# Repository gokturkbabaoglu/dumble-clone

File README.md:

# 12 V gitar amfisi — BF245B JFET + LM386 + TDA2003, ISF ton kontrolü

12 V ile çalışan, 4 Ω 6,5" full range hoparlör süren küçük bir pratik amfisi. Drive, Gain, ISF (US ↔ UK karakter), Volume kontrolleri, Dark/Normal/Bright anahtarı ve kesicili 3,5 mm kulaklık çıkışı var. Tek yüzlü, ev yapımı baskı devre; pot, jak ve LED kartın ön kenarına lehimli.

> Bu repo yalnızca bu 12 V JFET/op-amp amfisi içindir. Lambalı 5F1 amfi projesi ayrıdır.

## Durum (20 Kasım 2026)

- **Güncel kart: kart v5** — [`guncel/kicad/`](guncel/kicad/) (KiCad 10, proje `amfi_yeni.kicad_pro`). KiCad'de sıfırdan yeni tasarım: tellerle çizilmiş şema (ERC 0 hata / 0 uyarı), büyük padli ayak izi kütüphanesi (lazerle boya yakma + asit için), 185 × 96 mm tek yüz (yalnız alt bakır), ince yollar (0,4 mm, aralık 0,4 mm).
- **Açık işler:** 2 bağlantı henüz çizilmedi (U2.4–TOUT, R22–R31). Yollar KiCad'de elle kalınlaştırılıp düzenlenecek.
- Parçalar alındı. Kart henüz basılmadı, devre henüz denenmedi.
- Devre (netlist) Rev 5 + RV4 DRIVE; simülasyonları [`guncel/sim/`](guncel/sim/README.md).

## Klasörler

| Klasör | İçerik |
|---|---|
| [`guncel/kicad/`](guncel/kicad/) | **Güncel KiCad projesi (kart v5):** şema, kart, ayak izi kütüphanesi `amfi_yeni.pretty`, üretim/denetim betikleri |
| [`guncel/sim/`](guncel/sim/README.md) | Micro-Cap 12 simülasyonları: DC, AC, transient, THD, gürültü, empedans/kararlılık, C9/RV4, diğer amfilerle karşılaştırma |
| [`guncel/parca-gorselleri/`](guncel/parca-gorselleri/) | Jak, anahtar ve soğutucu ürün görselleri/ölçü çizimleri |
| [`eski/`](eski/README.md) | Önceki kartlar (v1, v2, v3 taslağı, v4 KiCad/Freerouting) ve araçları — kullanılmıyor, arşiv |

## Kontroller

| Kontrol | Parça | Ne yapar |
|---|---|---|
| Drive | RV4 B2.2K lineer + C9 22µ | JFET katının kazancı: ilk %70 temiz–sıcak, son %30 crunch–overdrive |
| Gain | B100K + R7 15k | LM386 katına giren sinyal; düşükte temiz, yüksekte crunch |
| SW1 | Mavi ON-OFF-ON | Yukarı Bright (470p) / orta Normal / aşağı Dark (3,3n) |
| ISF | B250K | Bir uç US (Fender tipi), öbür uç UK (Marshall tipi) |
| Volume | B500K | Güç katına giden seviye |
| Kulaklık | PJ-324M (kesicili) | Fiş takılınca hoparlör susar; L-pad (10 Ω / 330 Ω) |
| Güç | Kırmızı ON-ON, 6 bacak | Yukarı = açık |

- **Sinyal yolu:** gitar → Q1 BF245B → Gain + Dark/Bright → LM386 (≈38×) → ISF (iki sabit ton yığını arasında geçiş) → Volume → 47k/10k bölücü + ≈6 kHz alçak geçiren → TDA2003 (≈40 dB) → hoparlör / kulaklık
- **Besleme:** 12 V / 2 A adaptör → panel DC jak → TB1 → 1 A sigorta → güç anahtarı → 1N5822 → V12; RC filtrelerle LM386 (100 Ω) ve JFET (1k) beslemeleri ayrılır

## Kablolama

Kabloyla bağlanan parçalar: SW1 (Dark/Normal/Bright), güç anahtarı, panel DC jak ve hoparlör.

- **SW1** → P1 (B), P2 (orta), P3 (A). Bacaklar dikey takılır: üst = A (Dark), orta = ortak, alt = B (Bright). Kol yukarı = Bright.
- **Güç anahtarı** → P4 / P5: tek sütunun orta ve alt bacakları kullanılır (orta = sigortadan sonra, alt = 1N5822'ye). Kol yukarı = açık.
- **DC jak** → TB1, **hoparlör** → TB2 (kulaklık jakının kesici kontağından gelir). Hoparlör kabloları hoparlörde lehimlenir, kablolar burgulanır.

## Parça listesi (takılacak haliyle)

★ = tasarımdan farklı; çalışmayı bozmadığı için böyle bırakıldı (notlar aşağıda).

**Dirençler**

| Değer | Adet | Referanslar |
|---|---|---|
| 1 Ω | 1 | R27 |
| 2,2 Ω | 1 | R26 |
| 10 Ω | 2 | R9, R28 |
| 100 Ω | 1 | R1 |
| 220 Ω | 1 | R25 |
| 330 Ω | 1 | R29 |
| 1k | 1 | R2 |
| 1,2k | 1 | R8 |
| 2,2k | 2 | R3, R31 |
| 4,7k | 1 | R17 |
| 6,8k | 2 | R4, R16 |
| 10k | 4 | R12, R24, R30, R5b ★ |
| 15k | 1 | R7 |
| 22k | 2 | R22, R5a ★ |
| 33k | 1 | R18 |
| 47k | 1 | R23 |
| 91k | 1 | R19 |
| 100k | 3 | R10, R11, R13 |
| 120k | 2 | R15, R20 |
| 150k | 1 | R14 |
| 470k | 1 | R21 |
| 1M | 1 | R6 |

**Kondansatörler** (elektrolitiklerin hepsi yeni alındı, 25 V)

| Değer | Tür | Adet | Referanslar |
|---|---|---|---|
| 220p (221) | seramik | 1 | C15 |
| 33p | seramik | 1 | C26 |
| 470p | seramik | 2 | CB1, C18 |
| 3,3n | film | 2 | CD1, C21 |
| 22n | film | 2 | C19, C20 |
| 47n | film | 2 | C13, C17 |
| 100n | film | 6 | C2, C4, C6, C10, C16, C24 |
| 1µ | elektrolitik | 1 | C22 ★ |
| 4,7µ | elektrolitik | 1 | C14 |
| 10µ | elektrolitik | 2 | C11, C12 |
| 22µ | elektrolitik | 1 | C9 ★ (RV4 ile seri) |
| 100µ | elektrolitik | 2 | C5, C8 |
| 220µ | elektrolitik | 1 | C3 |
| 470µ | elektrolitik | 1 | C23 |
| 1000µ | elektrolitik | 1 | C7 |
| 2200µ | elektrolitik | 2 | C1, C25 |

**Diğer**

| Parça | Adet | Referans |
|---|---|---|
| BF245B | 1 | Q1 |
| LM386 + DIP-8 soket | 1 | U1 |
| TDA2003 + klips soğutucu | 1 | U2 (soğutucu kartın arka kenarından taşar) |
| 1N5822 | 1 | D1 |
| Sarı LED (+ R3 2,2k) | 1 | D2 |
| 10k trimer | 1 | TR1 (drain ≈7 V'a ayarlanır) |
| B100K / B250K / B500K pot, 16 mm (WH148 tipi) | 1/1/1 | RV1 / RV2 / RV3 |
| B2.2K pot (lineer) | 1 | RV4 ★ DRIVE (C9 ile seri) |
| 6,35 mm mono jak | 1 | J1 |
| PJ-324M | 1 | J2 |
| Vidalı klemens, 2'li | 2 | TB1, TB2 |
| Sigorta yuvası + 1 A sigorta | 1 | F1 ★ |
| Mavi ON-OFF-ON anahtar | 1 | SW1 |
| Kırmızı ON-ON 6 bacaklı anahtar | 1 | Güç |
| Panel DC jak, 3 uçlu | 1 | — |
| Bakır plaket 20 × 20 cm | 1 | — |
| M3 vida / mesafe | 5 | MH1–MH5 |
| Tel köprü (0,6 mm bakır tel) | 1 | JP1 — 5,08 mm (giriş susturma köprüsü) |
| 4 Ω 6,5" full range kâğıt hoparlör | 1 | Kablolar hoparlörün üzerinde lehimlenir, karta TB2 ile bağlanır |
| 12 V / 2 A adaptör | 1 | — |
| Kutu ve pot düğmeleri | — | 3D baskı |

**Düzenleme notları**

- **R5 33k → 22k + 10k seri ★**: ters U şeklinde R5 deliklerine. Tek 33k R18'e gider.
- **R20 + R30 = 120k + 10k, R22 + R31 = 22k + 2,2k**: kartta ayrı parçalar.
- **C22 ★ = 1 µF elektrolitik**: + ucu TDA2003 tarafına (TIN); kartta Ø5 mm / 2,0 mm elektrolitik yeri.
- **C9 + RV4 DRIVE ★**: C9 22 µF artık takılıyor ve RV4 ile seri bağlanıyor (bu seri kol TR1'e paralel): SRC → C9 (+ ucu SRC'de) → RV4 B2.2K (değişken direnç; uç + slider birleşik) → GND. RV4 yalnızca AC kazancı ayarlar, TR1 ile kurulan DC çalışma noktası (drain ≈ 7 V) değişmez. Simülasyon: JFET kazancı ×3.1 (tam sol, normal çalmada temiz) → ×10.8 (tam sağ, overdrive); düğmenin ilk %70'i temiz–sıcak, son %30'u crunch–overdrive. B2.2K pot alındı. Saat yönünde direnç azalacak şekilde bağlanır. Kartta ön kenarda, J1 ile Gain arasında.
- **Potlar B ★**: A pot alınmadı; Gain için R7 15k (slider–GND) takılır.
- **Sigorta ★ 1 A normal (hızlı)**: tasarımda yavaş atan öngörülmüştü. Açılışta atarsa 1–2 A yavaş atan sigortaya geç.
- **Elektrolitikler**: hepsi yeni, 25 V (en az 16 V gerekli; görünüm aynı olsun diye hepsi yenilendi).

**Montaj ve kart yapımı malzemeleri**

- TR1: 10k çok turlu trimer, 3296W tipi.
- Elektrolitikler 105 °C, aynı seri; C1, C7, C25 için mümkünse low ESR.
- TDA2003 için termal macun, M3 vida/somun; kartı kutuya sabitlemek için M3 aralayıcılar.
- Hoparlör kablosu 0,5–0,75 mm² ikili (≈50 cm); DC jak kablosu 0,5 mm² kırmızı/siyah (≈30 cm, burgulanacak); köprü teli izoleli tek damar (≈1 m); makaron; kablo bağı.
- Kart yapımı: perklorür ya da sodyum persülfat, parlak kâğıt (toner transfer), aseton/tiner, matkap uçları 0,8 / 1,0 / 1,2 / 1,5 mm ve montaj delikleri için 3,2 mm.

## Eski rapor ve bağlantılar

- Eski devir raporları (v2/v3 ve v4 dönemi) ve eski kartın teslim raporu: [`eski/`](eski/README.md).

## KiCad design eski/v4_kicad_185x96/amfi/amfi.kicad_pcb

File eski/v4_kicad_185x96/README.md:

# Kart v4 — KiCad + Freerouting, 185 × 96 mm (arşiv)

> **Eski sürüm.** Yerini kart v5 aldı: [`../../guncel/kicad/`](../../guncel/kicad/). Bu klasör yalnızca arşiv içindir.

KiCad 10'da `../v2_v3/araclar/design2.py` netlistinden üretilen, Freerouting ile yönlendirilen kart. GND dolgusu, 2 tel köprü (K1, K2). 18 Kasım'da yerleşim aynı kalarak yollar 1–2,5 mm'ye kalınlaştırıldı (eski PR #12, `kalin-yollar` dalı). Toner transferde sorun çıkınca kart v5'e geçildi.

| Klasör / dosya | İçerik |
|---|---|
| `amfi/` | KiCad projesi (`amfi.kicad_pro`; şema, kalınlaştırılmış kart, kütüphane, kurallar) |
| `cikti/` | Toner A4 1:1 PDF, parça yerleşimi PDF, lazer dosyaları (`lazer/`), teslim raporu (`TESLIM_RAPORU.md`) |
| `gorseller/` | Kart görseli, toner önizlemesi, yol kalınlığı haritası |
| `*.py`, `kopruler.json` | Üretim, yerleşim, toplu yönlendirme, analiz, köprü, kalınlaştırma ve PDF betikleri |

KiCad 10 projesi `amfi/` klasöründe (`amfi.kicad_pro`). Şema, sembol ve ayak izi kütüphanesi `gen_kicad.py` ile `../v2_v3/araclar/design2.py` netlistinden üretilir; elle çizilmedi.

| Konu | Değer |
|---|---|
| Boyut | 185 × 96 mm (ön kenar = panel; v3'e göre 18 mm daha kısa) |
| Bakır | Yalnız B.Cu (alt). Üst katta yol/via yasak (kural alanı + `amfi.kicad_dru`) |
| GND | Alt katın tamamında dolgu, padler dolguya doğrudan (termal kolsuz) bağlı. Sinyal yolları Freerouting'le çizildi, GND'yi dolgu bağlar |
| Tel köprüler | K1 (D2 tarafındaki GND adası) ve K2 (C3 tarafındaki GND adası), ikisi de 5,08 mm, düz; parça gövdesi üstünden geçmez, sinyal netlerinde köprü yok |
| Yol genişliği | **Kalınlaştırıldı (18 Kasım):** yerleşim aynı, her yol 0,5 mm aralığı bozmadan sığdığı kadar genişletildi — uzunluğun %43'ü 2–2,5 mm, %16'sı 1,5–2 mm, %38'i 1,0–1,5 mm (sıkışık bölgeler), %2'si 1 mm altı (eski dar pin girişleri). Padler sığan yerlerde 1 mm halkaya büyütüldü. Harita: `gorseller/yol_kalinlik_haritasi.png` |
| Aralık / kenar | Bakır–bakır ≥ 0,5 mm; arka/sol/sağ kenarda 1 mm yolsuz şerit, ön kenarda (potların altı) 0,5 mm |
| Vida delikleri | M3 × 5: arka kenarda 3, ön tarafta 2 (MH4 J1'in arkasında, MH5 güç anahtarının arkasında) |
| Ön panel sırası | Değişmedi: J1, RV4, RV1, SW1, RV2, RV3, J2, LED, güç anahtarı |

**Gürültü ölçütleri (seçilen kart):** giriş yolu J1 → R5 → Q1 gate 33 mm; giriş netlerine en yakın güç/çıkış yolu 110 mm; hoparlör akım döngüsü (TDA çıkışı → C25 → hoparlör → GND) 374 mm²; TDA girişi (TIN) yolu 55 mm; giriş katı solda, güç katı sağ arkada, besleme sağ kenarda.

**Çıktılar:**
- `cikti/toner_alt_bakir_1e1_A4.pdf` — toner transfer için B.Cu, A4, 1:1, vektör, delik merkez işaretli. Aynalamadan, %100 bas.
- `cikti/parca_yerlesimi_A4.pdf` — parça yüzü yerleşimi (serigrafi), A4.
- `cikti/lazer/` — lazerle boya yakma / kazıma için 1:1 dosyalar: aynalı 1000 dpi PNG ve SVG, üstten SVG, DXF; açıklama `OKUBENI.txt`.

**Kalınlaştırma betikleri:** `kalinlastir.py` (yolları/padleri aralığı koruyarak büyütür, GND dolgusunun bölünmemesini `dolgu.py` ile denetler), `son.py` (KiCad konsolunda dolgu + DRC + A4 PDF), `gorsel.py` (önizleme ve lazer dosyaları), `genislet.py` (yardımcı geometri).

**Parça adı değişiklikleri (KiCad harf sonekini kabul etmediği için):** C15a → C15, C15b → C26, R20a → R20, R20b → R30, R22a → R22, R22b → R31; KiCad'de CB → CB1, CD → CD1, anahtar kablo padleri P_SWB/P_SWC/P_SWD → P1/P2/P3, P_PW1/P_PW2 → P4/P5. Yeni: MH4, MH5 (vida), K1, K2 (tel köprü).

**Nasıl üretildi:** `yerlesim.py` (elle düşünülmüş yerleşim tohumları + çakışma çözücü) → `toplu.py` (KiCad konsolunda Freerouting'i toplu, penceresiz çalıştırır) → `analiz.py` (kopuk bağlantı, GND adaları, gürültü ölçütleri) → `kopru.py` / `kopru_ekle.py` (GND adaları için en kısa düz köprü). `cikti.py` KiCad konsolunda toner (B.Cu, 1:1) ve parça yerleşimi PDF'lerini `cikti/` klasörüne üretir. Seçilen yerleşim: `KART_H=96 python yerlesim.py "K4@96#11"`. 185 mm genişlikte 114 → 84 mm arası yaklaşık 150 kart denendi; 96 mm, tamamen yönlendirilmiş ve en az köprü (2) isteyen en küçük karttı.

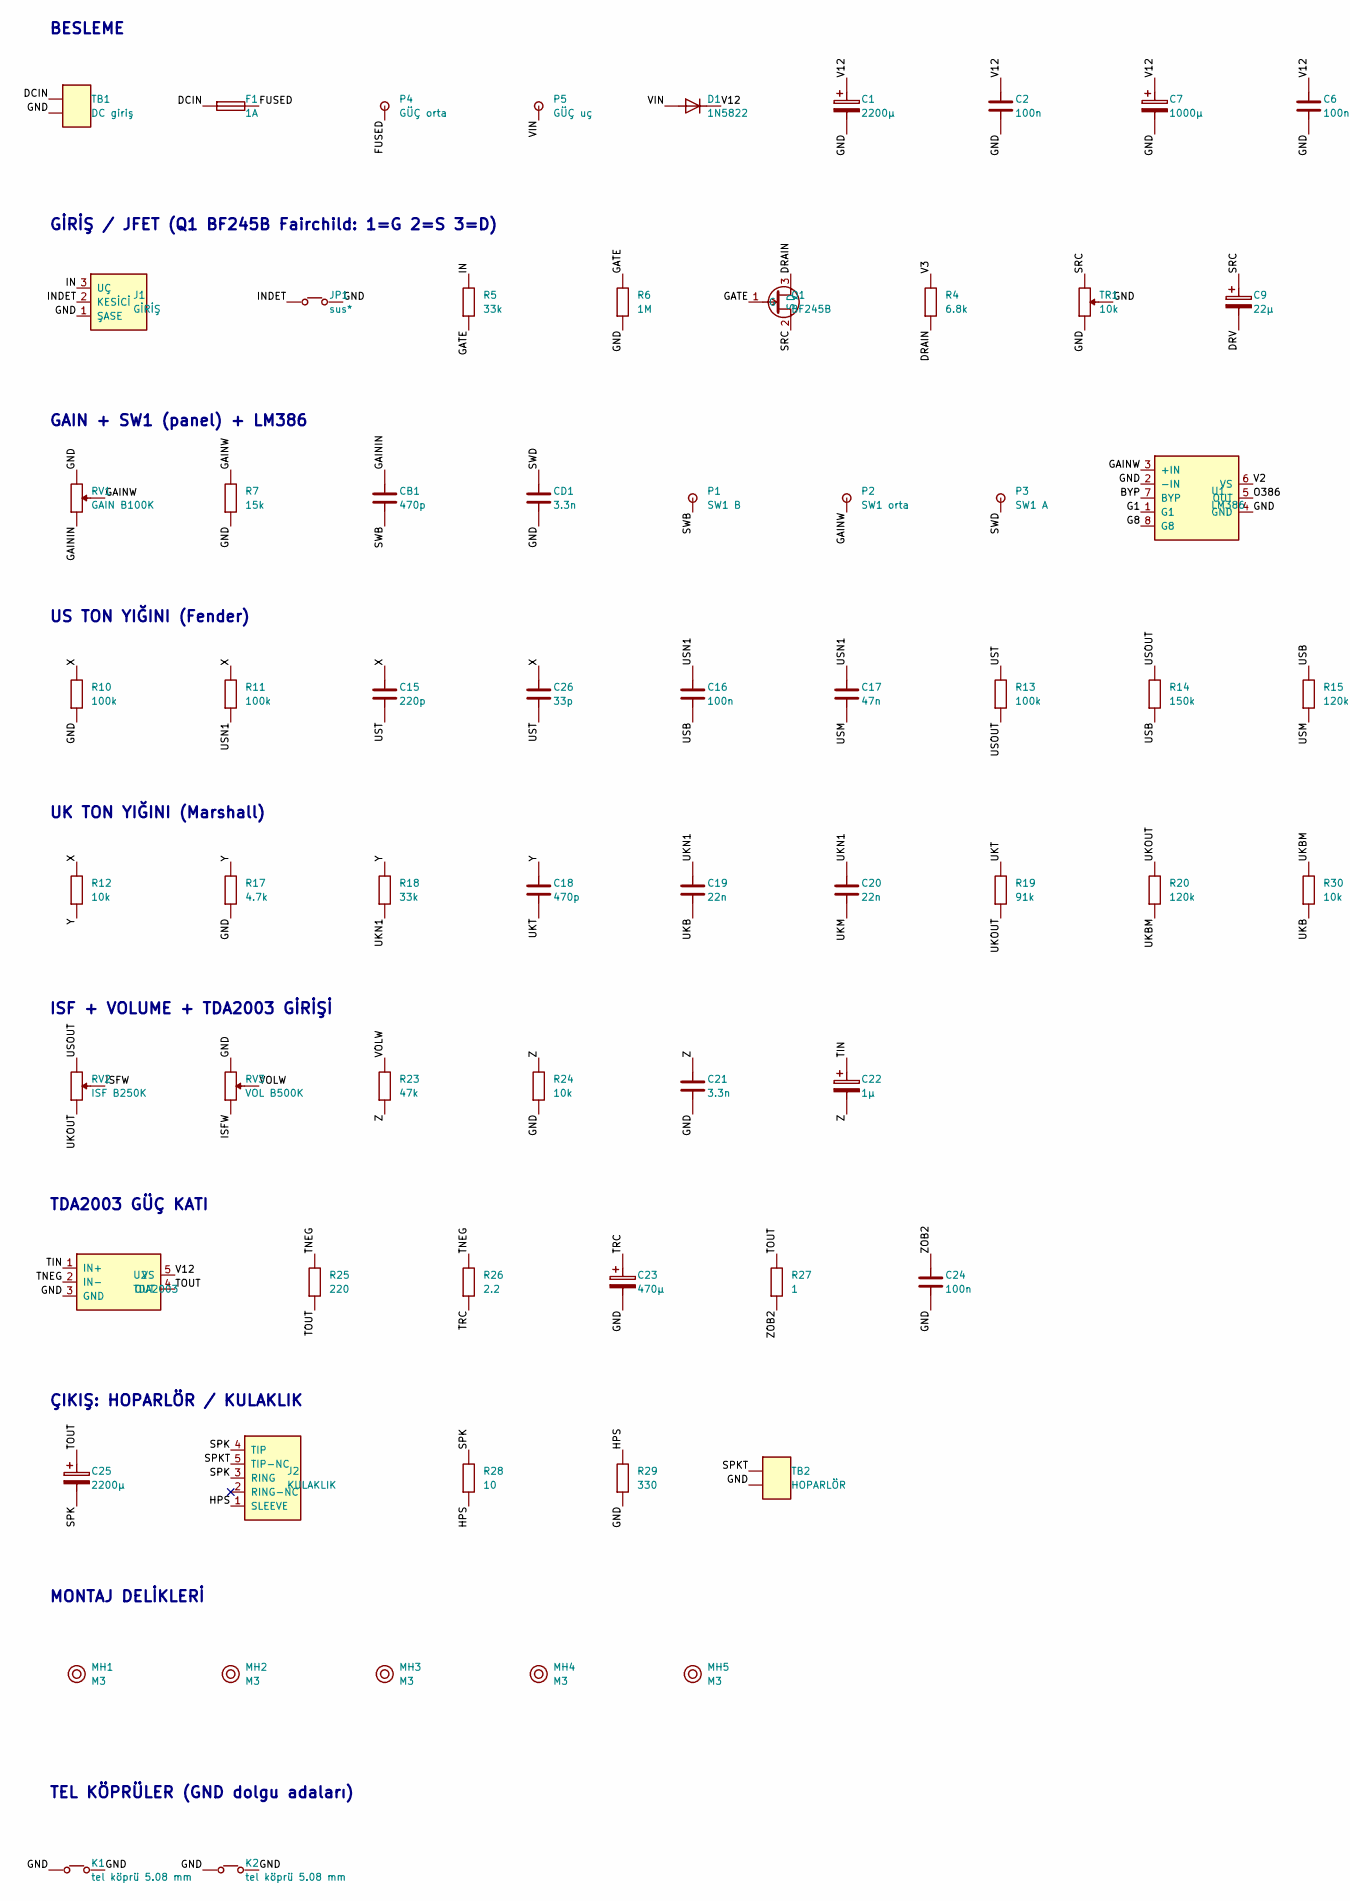
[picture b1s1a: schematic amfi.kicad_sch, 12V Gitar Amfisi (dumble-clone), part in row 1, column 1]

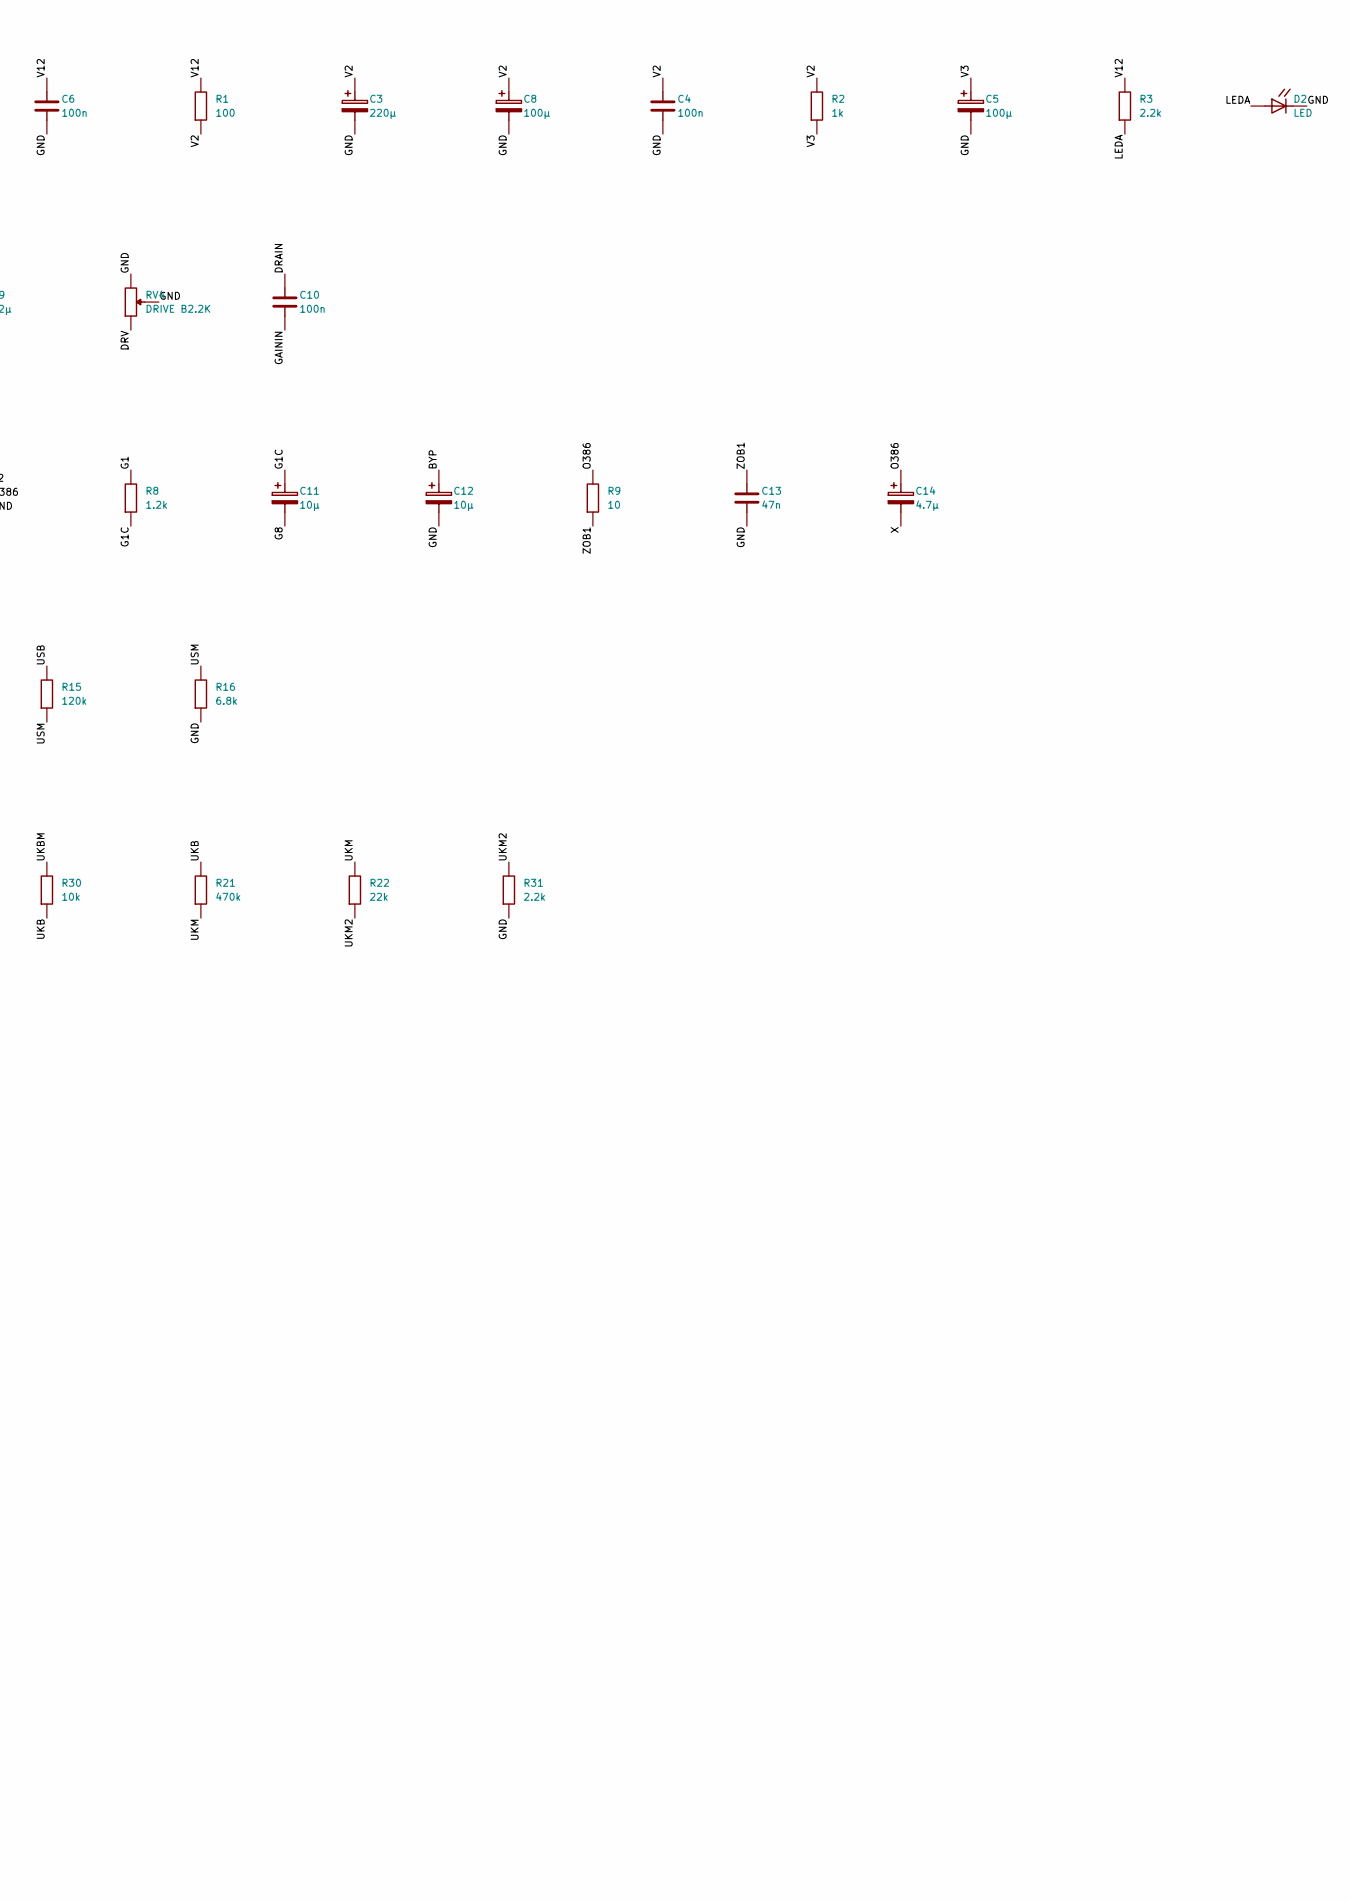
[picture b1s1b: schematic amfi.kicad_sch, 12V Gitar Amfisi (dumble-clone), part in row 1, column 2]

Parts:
C1, C25: 2200µ; CP_D12.5_P5
C2, C4, C6, C10, C16, C24: 100n; C_Film_P5.08
C3: 220µ; CP_D6.3_P2.5
C5, C8: 100µ; CP_D5_P2
C7: 1000µ; CP_D10_P5
C9: 22µ; CP_D5_P2
C11, C12: 10µ; CP_D5_P2
C13, C17: 47n; C_Film_P5.08
C14: 4.7µ; CP_D5_P2
C15: 220p; C_Disc_P5.08
C18: 470p; C_Disc_P5.08
C19, C20: 22n; C_Film_P5.08
C21: 3.3n; C_Film_P5.08
C22: 1µ; CP_D5_P2
C23: 470µ; CP_D8_P3.5
C26: 33p; C_Disc_P5.08
CB1: 470p; C_Disc_P5.08
CD1: 3.3n; C_Film_P5.08
D1: 1N5822; DO201_P15.24
D2: LED; LED_5mm_Dik90
F1: 1A; Sigorta_23x9_P10
J1: GİRİŞ; Jak_6.35_Mono
J2: KULAKLIK; PJ-324M
JP1: sus*; Jumper_P5.08
K1, K2: tel köprü 5.08 mm; Kopru_P5.08
MH1, MH2, MH3, MH4, MH5: M3; MH_M3
P1: SW1 B; Pad_Kablo
P2: SW1 orta; Pad_Kablo
P3: SW1 A; Pad_Kablo
P4: GÜÇ orta; Pad_Kablo
P5: GÜÇ uç; Pad_Kablo
Q1: BF245B; TO92_Inline_GSD
R1: 100; R_P10.16
R2: 1k; R_P10.16
R3, R31: 2.2k; R_P10.16
R4, R16: 6.8k; R_P10.16
R5, R18: 33k; R_P10.16
R6: 1M; R_P10.16
R7: 15k; R_P10.16
R8: 1.2k; R_P10.16
R9, R28: 10; R_P10.16
R10, R11, R13: 100k; R_P10.16
R12, R24, R30: 10k; R_P10.16
R14: 150k; R_P10.16
R15, R20: 120k; R_P10.16
R17: 4.7k; R_P10.16
R19: 91k; R_P10.16
R21: 470k; R_P10.16
R22: 22k; R_P10.16
R23: 47k; R_P10.16
R25: 220; R_P10.16
R26: 2.2; R_P10.16
R27: 1; R_P10.16
R29: 330; R_P10.16
RV1: GAIN B100K; Pot_WH148_16mm
RV2: ISF B250K; Pot_WH148_16mm
RV3: VOL B500K; Pot_WH148_16mm
RV4: DRIVE B2.2K; Pot_WH148_16mm
TB1: DC giriş; Klemens_2_P5.08
TB2: HOPARLÖR; Klemens_2_P5.08
TR1: 10k; Trim_3296W
U1: LM386; DIP8_Socket
U2: TDA2003; Pentawatt_V

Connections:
BYP: C12.1 (+), U1.7 (BYP)
DCIN: F1.1, TB1.1
DRAIN: C10.1, Q1.3 (D), R4.2
DRV: C9.2 (-), RV4.3
FUSED: F1.2, P4.1
G1: R8.1, U1.1 (G1)
G1C: C11.1 (+), R8.2
G8: C11.2 (-), U1.8 (G8)
GAININ: C10.2, CB1.1, RV1.3
GAINW: P2.1, R7.1, RV1.2, U1.3 (+IN)
GATE: Q1.1 (G), R5.2, R6.1
GND: C1.2 (-), C2.2, C3.2 (-), C4.2, C5.2 (-), C6.2, C7.2 (-), C8.2 (-), C12.2 (-), C13.2, C21.2, C23.2 (-), C24.2, CD1.2, D2.2 (K), J1.1 (ŞASE), JP1.2, K1.1, K1.2, K2.1, K2.2, R6.2, R7.2, R10.2, R16.2, R17.2, R24.2, R29.2, R31.2, RV1.1, RV3.1, RV4.1, RV4.2, TB1.2, TB2.2, TR1.2, TR1.3, U1.2 (-IN), U1.4 (GND), U2.3 (GND)
HPNC2: J2.2 (RING-NC)
HPS: J2.1 (SLEEVE), R28.2, R29.1
IN: J1.3 (UÇ), R5.1
INDET: J1.2 (KESİCİ), JP1.1
ISFW: RV2.2, RV3.3
LEDA: D2.1 (A), R3.2
O386: C14.1 (+), R9.1, U1.5 (OUT)
SPK: C25.2 (-), J2.3 (RING), J2.4 (TIP), R28.1
SPKT: J2.5 (TIP-NC), TB2.1
SRC: C9.1 (+), Q1.2 (S), TR1.1
SWB: CB1.2, P1.1
SWD: CD1.1, P3.1
TIN: C22.1 (+), U2.1 (IN+)
TNEG: R25.1, R26.1, U2.2 (IN-)
TOUT: C25.1 (+), R25.2, R27.1, U2.4 (OUT)
TRC: C23.1 (+), R26.2
UKB: C19.2, R21.1, R30.2
UKBM: R20.2, R30.1
UKM: C20.2, R21.2, R22.1
UKM2: R22.2, R31.1
UKN1: C19.1, C20.1, R18.2
UKOUT: R19.2, R20.1, RV2.3
UKT: C18.2, R19.1
USB: C16.2, R14.2, R15.1
USM: C17.2, R15.2, R16.1
USN1: C16.1, C17.1, R11.2
USOUT: R13.2, R14.1, RV2.1
UST: C15.2, C26.2, R13.1
V2: C3.1 (+), C4.1, C8.1 (+), R1.2, R2.1, U1.6 (VS)
V3: C5.1 (+), R2.2, R4.1
V12: C1.1 (+), C2.1, C6.1, C7.1 (+), D1.2 (K), R1.1, R3.1, U2.5 (VS)
VIN: D1.1 (A), P5.1
VOLW: R23.1, RV3.2
X: C14.2 (-), C15.1, C26.1, R10.1, R11.1, R12.1
Y: C18.1, R12.2, R17.1, R18.1
Z: C21.1, C22.2 (-), R23.2, R24.1
ZOB1: C13.1, R9.2
ZOB2: C24.1, R27.2

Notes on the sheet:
BESLEME
GİRİŞ / JFET (Q1 BF245B Fairchild: 1=G 2=S 3=D)
GAIN + SW1 (panel) + LM386
US TON YIĞINI (Fender)
UK TON YIĞINI (Marshall)
ISF + VOLUME + TDA2003 GİRİŞİ
TDA2003 GÜÇ KATI
ÇIKIŞ: HOPARLÖR / KULAKLIK
MONTAJ DELİKLERİ
TEL KÖPRÜLER (GND dolgu adaları)

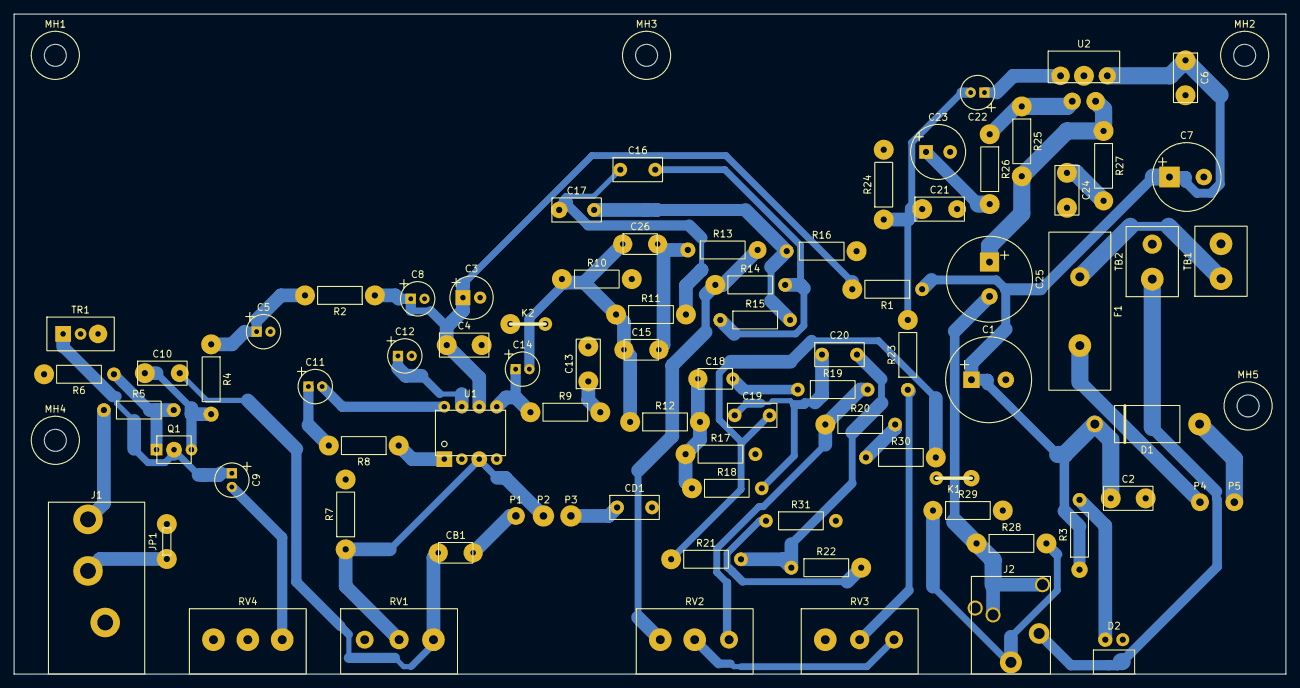
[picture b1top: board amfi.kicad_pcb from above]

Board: 2 copper layers, 185.0 x 96.0 mm, 87 parts (0 on the bottom side), 49 nets.

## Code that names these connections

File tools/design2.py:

import sys, os, math
sys.path.insert(0, os.path.dirname(os.path.abspath(__file__)))
from params import *
U = 1.27
def mk(pins, body, pad, hole=None, shape='rect'):
    return dict(pins=pins, body=body, pad=pad, hole=hole or (0.9 if pad < 2.1 else (1.1 if pad < 2.5 else 1.3)), shape=shape)
FP = {}
FP['R'] = mk([(0,0),(10.16,0)], ('rect',6.5,2.6), 2.0, 0.9)
FP['CF'] = mk([(0,0),(5.08,0)], ('rect',7.2,3.5), 2.0, 0.9)
FP['CC'] = mk([(0,0),(5.08,0)], ('rect',5.0,3.0), 1.9, 0.8)   # seramik pF
for k,(d,p) in ELKO.items():
    pad,hole=ELKO_PAD[p]
    FP['E'+k] = mk([(0,0),(p,0)], ('circ',d), pad, hole)
FP['TO92'] = mk([(0,0),(2.54,0),(5.08,0)], ('to92',5.0,4.0), 1.7, 0.8)
FP['TRIM'] = mk([(0,0),(2.54,0),(5.08,0)], ('rect',9.8,4.9), 1.7, 0.8)
FP['DIP8'] = mk([(0,0),(2.54,0),(5.08,0),(7.62,0),(7.62,-7.62),(5.08,-7.62),(2.54,-7.62),(0,-7.62)], ('dip',10.2,6.6), 1.7, 0.8)
FP['DO201'] = mk([(0,0),(15.24,0)], ('rect',9.5,5.4), 2.4, 1.3)
FP['PW5'] = mk([(-3.4,0),(-1.7,3.7),(0,0),(1.7,3.7),(3.4,0)], ('pw',10.4,4.6), 1.9, 1.0)
FP['PAD'] = mk([(0,0)], None, 2.6, 1.1)
FP['KO1'] = mk([(0,0)], ('front',15.0,20.0), 0.01, 0.0)
FP['KO2'] = mk([(0,0)], ('front',17.0,22.0), 0.01, 0.0)
FP['MH'] = mk([(0,0)], ('circ',7.0), 5.6, 3.2)
FP['JMP'] = mk([(0,0),(5.08,0)], ('rect',4.0,1.2), 2.0, 0.9)     # tel köprü (JP1)
# front parts: pin offsets relative to axis point on front edge; local frame: +y = toward back (north) -> image -Y
def front(pins_depth_lat, body, pad, hole, shape):
    # (depth from front face, lateral) -> image offset (X=lateral... ) ; drawing lateral + (up in top view, front left) maps to image -X
    return mk([(-lat, -dep) for dep,lat in pins_depth_lat], body, pad, hole, shape)
FP['J635'] = front([(J635_PIN_FROM_FRONT[i], J635_LATERAL[i]) for i in range(3)], ('front',)+J635_BODY, J635_PAD, J635_HOLE, 'oval')
FP['PJ324'] = front([PJ324[i] for i in (1,2,3,4,5)], ('front',)+PJ324_BODY, PJ324_PAD, PJ324_HOLE, 'round')
FP['POT'] = mk([(-POT_PITCH,-POT_SETBACK),(0,-POT_SETBACK),(POT_PITCH,-POT_SETBACK)], ('front',)+POT_BODY, POT_PAD, POT_HOLE)
FP['LED'] = mk([(-LED_PITCH/2,-LED_SETBACK),(LED_PITCH/2,-LED_SETBACK)], ('front',LED_D+1,LED_SETBACK-1.5), 1.9, 0.9)
FP['FUSE'] = mk([(0,0),(FUSE_PITCH,0)], ('rectc',)+FUSE_BODY, FUSE_PAD, FUSE_HOLE)
FP['TB2'] = mk([(0,0),(TB_PITCH,0)], ('rectc',)+TB_BODY, TB_PAD, TB_HOLE)
# ------------------------------- NETLIST -------------------------------
C = {
 # power
 'TB1':('TB2','DC giriş',['DCIN','GND']),
 'F1':('FUSE','1A',['DCIN','FUSED']),
 'D1':('DO201','1N5822',['VIN','V12']),
 'C1':('E2200µ','2200µ',['V12','GND']),
 'C2':('CF','100n',['V12','GND']),
 'R1':('R','100',['V12','V2']),
 'C3':('E220µ','220µ',['V2','GND']),
 'C8':('E100µ','100µ',['V2','GND']),
 'C4':('CF','100n',['V2','GND']),
 'R2':('R','1k',['V2','V3']),
 'C5':('E100µ','100µ',['V3','GND']),
 'R3':('R',R3_LED,['V12','LEDA']),
 'D2':('LED','LED',['LEDA','GND']),
 # input / jfet
 'J1':('J635','GİRİŞ',[{'GND':'GND','INDET':'INDET','IN':'IN'}[f] for f in J635_FUNC]),
 'JP1':('JMP','sus*',['INDET','GND']),
 'R5':('R','33k',['IN','GATE']),
 'R6':('R','1M',['GATE','GND']),
 'Q1':('TO92','BF245B',['GATE','SRC','DRAIN']),     # Fairchild (parça üzerinde F logosu): 1=G 2=S 3=D
 'TR1':('TRIM','10k',['SRC','GND','GND']),
 'C9':('E22µ','22µ',['SRC','DRV']),
 'RV4':('POT','DRIVE B2.2K',['GND','GND','DRV']),   # saat yönü = direnç azalır = daha çok kazanç
 'R4':('R','6.8k',['V3','DRAIN']),
 'C10':('CF','100n',['DRAIN','GAININ']),
 # gain + sw1
 'RV1':('POT','GAIN B100K',['GND','GAINW','GAININ']),
 'R7':('R','15k',['GAINW','GND']),
 'CB':('CC','470p',['GAININ','SWB']),
 'CD':('CF','3.3n',['SWD','GND']),
 'P_SWB':('PAD','SW1 B',['SWB']),'P_SWC':('PAD','SW1 orta',['GAINW']),'P_SWD':('PAD','SW1 A',['SWD']),
 # lm386
 'U1':('DIP8','LM386',['G1','GND','GAINW','GND','O386','V2','BYP','G8']),
 'R8':('R','1.2k',['G1','G1C']),
 'C11':('E10µ','10µ',['G1C','G8']),
 'C12':('E10µ','10µ',['BYP','GND']),
 'R9':('R','10',['O386','ZOB1']),
 'C13':('CF','47n',['ZOB1','GND']),
 'C14':('E4.7µ','4.7µ',['O386','X']),
 # US stack
 'R10':('R','100k',['X','GND']),
 'R11':('R','100k',['X','USN1']),
 'C15':('CC','220p',['X','UST']),
 'C26':('CC','33p',['X','UST']),
 'C16':('CF','100n',['USN1','USB']),
 'C17':('CF','47n',['USN1','USM']),
 'R13':('R','100k',['UST','USOUT']),
 'R14':('R','150k',['USOUT','USB']),
 'R15':('R','120k',['USB','USM']),
 'R16':('R','6.8k',['USM','GND']),
 # UK stack
 'R12':('R','10k',['X','Y']),
 'R17':('R','4.7k',['Y','GND']),
 'R18':('R','33k',['Y','UKN1']),
 'C18':('CC','470p',['Y','UKT']),
 'C19':('CF','22n',['UKN1','UKB']),
 'C20':('CF','22n',['UKN1','UKM']),
 'R19':('R','91k',['UKT','UKOUT']),
 'R20':('R','120k',['UKOUT','UKBM']),
 'R30':('R','10k',['UKBM','UKB']),
 'R21':('R','470k',['UKB','UKM']),
 'R22':('R','22k',['UKM','UKM2']),
 'R31':('R','2.2k',['UKM2','GND']),
 # ISF + volume pots
 'RV2':('POT','ISF B250K',['USOUT','ISFW','UKOUT']),
 'RV3':('POT','VOL B500K',['GND','VOLW','ISFW']),
 'R23':('R','47k',['VOLW','Z']),
 'R24':('R','10k',['Z','GND']),
 'C21':('CF','3.3n',['Z','GND']),
 'C22':('E1µ','1µ',['TIN','Z']),          # elektrolitik: + (1. bacak) TIN tarafı
 # TDA
 'U2':('PW5','TDA2003',['TIN','TNEG','GND','TOUT','V12']),
 'R25':('R','220',['TNEG','TOUT']),
 'R26':('R','2.2',['TNEG','TRC']),
 'C23':('E470µ','470µ',['TRC','GND']),
 'R27':('R','1',['TOUT','ZOB2']),
 'C24':('CF','100n',['ZOB2','GND']),
 'C6':('CF','100n',['V12','GND']),
 'C7':('E1000µ','1000µ',['V12','GND']),
 'C25':('E2200µ','2200µ',['TOUT','SPK']),
 # headphone / speaker
 'J2':('PJ324','KULAKLIK',['HPS','HPNC2','SPK','SPK','SPKT']),   # 1 sleeve,2 ring-NC,3 ring,4 tip,5 tip-NC
 'R28':('R','10',['SPK','HPS']),
 'R29':('R','330',['HPS','GND']),
 'TB2':('TB2','HOPARLÖR',['SPKT','GND']),
 # power switch pads (panel switch)
 'P_PW1':('PAD','GÜÇ orta',['FUSED']),'P_PW2':('PAD','GÜÇ uç',['VIN']),
 'KO_SW1':('KO1','SW1 gövdesi',['NC_KO1']),'KO_SW2':('KO2','güç anahtarı gövdesi',['NC_KO2']),
 'MH1':('MH','M3',['NC_MH1']),'MH2':('MH','M3',['NC_MH2']),'MH3':('MH','M3',['NC_MH3']),
}
POWER_NETS={'V12','VIN','DCIN','FUSED','TOUT','SPK','SPKT','TNEG','TRC','ZOB2'}

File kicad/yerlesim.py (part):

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    P = GP.fixed()
    P.update({
        # --- TDA2003 güç katı (arka sağ; soğutucu arka kenardan taşar) ---
        'U2':  (156, 8.5, 0),       # pinler: 1 TIN (152.6) 2 TNEG 3 GND (156) 4 TOUT 5 V12 (159.4)
        'C6':  (167, 7, 270),     # V12 dekuplaj, 5. bacak yanında
        'C7':  (168, 23, 0),       # 1000µ V12
        'R27': (161, 15, 270),      # TOUT -> ZOB2
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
